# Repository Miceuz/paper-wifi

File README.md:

# Paper-WiFi

Wifi-enabled e-paper display for I2C sensors. Arduino compatible software on Platformio. 3D printable case.

## Specifications

 * MCU: ESP32C3
 * Power supply: 2xAA, 3V
 * Sleep current: 38uA
 * Screen size: 2.13"
 * Display resolution: 212(H) × 104(V) pixels
 * Connectivity: I2C, UART over USB, UART
 * GPIO: 2 
 * Sensors: Temperature, Relative humidity
 * Temperature accuracy: 0.2°C typical
 * Relative humidity accuracy: 1.8% typical

## Programming instructions

Firmware build and upload process is managed by [Platformio](https://platformio.org). Most probably you will encounter the board in deep sleep in which it is not visible via USB. Jump GPIO9 to GND and reset the board to put it into bootloader mode. Run `pio run -t upload` to compile and upload firmware. Remove jumper and reset the board to run. If deep sleep is not used, board can be programmed without GPIO9 jumper.

## MQTT backend infrastructure

 * To quickly see your data piping in follow this guide: [Getting started with MQTT](https://github.com/Miceuz/paper-wifi/tree/main/tutorials/Getting%20started%20with%20MQTT)
 * To setup your own backend for data storage and display follow this guide: [docker-compose-mosquitto-influxdb-telegraf-grafana](https://github.com/Miceuz/docker-compose-mosquitto-influxdb-telegraf-grafana)

## Licence

[CERN Open Hardware Licence Version 2 - Strongly Reciprocal](https://ohwr.org/cern_ohl_s_v2.txt)

![Build with PlatformIO](https://img.shields.io/badge/build%20with-PlatformIO-orange?logo=data%3Aimage%2Fsvg%2Bxml%3Bbase64%2CPHN2ZyB3aWR0aD0iMjUwMCIgaGVpZ2h0PSIyNTAwIiB2aWV3Qm94PSIwIDAgMjU2IDI1NiIgeG1sbnM9Imh0dHA6Ly93d3cudzMub3JnLzIwMDAvc3ZnIiBwcmVzZXJ2ZUFzcGVjdFJhdGlvPSJ4TWlkWU1pZCI+PHBhdGggZD0iTTEyOCAwQzkzLjgxIDAgNjEuNjY2IDEzLjMxNCAzNy40OSAzNy40OSAxMy4zMTQgNjEuNjY2IDAgOTMuODEgMCAxMjhjMCAzNC4xOSAxMy4zMTQgNjYuMzM0IDM3LjQ5IDkwLjUxQzYxLjY2NiAyNDIuNjg2IDkzLjgxIDI1NiAxMjggMjU2YzM0LjE5IDAgNjYuMzM0LTEzLjMxNCA5MC41MS0zNy40OUMyNDIuNjg2IDE5NC4zMzQgMjU2IDE2Mi4xOSAyNTYgMTI4YzAtMzQuMTktMTMuMzE0LTY2LjMzNC0zNy40OS05MC41MUMxOTQuMzM0IDEzLjMxNCAxNjIuMTkgMCAxMjggMCIgZmlsbD0iI0ZGN0YwMCIvPjxwYXRoIGQ9Ik0yNDkuMzg2IDEyOGMwIDY3LjA0LTU0LjM0NyAxMjEuMzg2LTEyMS4zODYgMTIxLjM4NkM2MC45NiAyNDkuMzg2IDYuNjEzIDE5NS4wNCA2LjYxMyAxMjggNi42MTMgNjAuOTYgNjAuOTYgNi42MTQgMTI4IDYuNjE0YzY3LjA0IDAgMTIxLjM4NiA1NC4zNDYgMTIxLjM4NiAxMjEuMzg2IiBmaWxsPSIjRkZGIi8+PHBhdGggZD0iTTE2MC44NjkgNzQuMDYybDUuMTQ1LTE4LjUzN2M1LjI2NC0uNDcgOS4zOTItNC44ODYgOS4zOTItMTAuMjczIDAtNS43LTQuNjItMTAuMzItMTAuMzItMTAuMzJzLTEwLjMyIDQuNjItMTAuMzIgMTAuMzJjMCAzLjc1NSAyLjAxMyA3LjAzIDUuMDEgOC44MzdsLTUuMDUgMTguMTk1Yy0xNC40MzctMy42Ny0yNi42MjUtMy4zOS0yNi42MjUtMy4zOWwtMi4yNTggMS4wMXYxNDAuODcybDIuMjU4Ljc1M2MxMy42MTQgMCA3My4xNzctNDEuMTMzIDczLjMyMy04NS4yNyAwLTMxLjYyNC0yMS4wMjMtNDUuODI1LTQwLjU1NS01Mi4xOTd6TTE0Ni41MyAxNjQuOGMtMTEuNjE3LTE4LjU1Ny02LjcwNi02MS43NTEgMjMuNjQzLTY3LjkyNSA4LjMyLTEuMzMzIDE4LjUwOSA0LjEzNCAyMS41MSAxNi4yNzkgNy41ODIgMjUuNzY2LTM3LjAxNSA2MS44NDUtNDUuMTUzIDUxLjY0NnptMTguMjE2LTM5Ljc1MmE5LjM5OSA5LjM5OSAwIDAgMC05LjM5OSA5LjM5OSA5LjM5OSA5LjM5OSAwIDAgMCA5LjQgOS4zOTkgOS4zOTkgOS4zOTkgMCAwIDAgOS4zOTgtOS40IDkuMzk5IDkuMzk5IDAgMCAwLTkuMzk5LTkuMzk4em0yLjgxIDguNjcyYTIuMzc0IDIuMzc0IDAgMSAxIDAtNC43NDkgMi4zNzQgMi4zNzQgMCAwIDEgMCA0Ljc0OXoiIGZpbGw9IiNFNTcyMDAiLz48cGF0aCBkPSJNMTAxLjM3MSA3Mi43MDlsLTUuMDIzLTE4LjkwMWMyLjg3NC0xLjgzMiA0Ljc4Ni01LjA0IDQuNzg2LTguNzAxIDAtNS43LTQuNjItMTAuMzItMTAuMzItMTAuMzItNS42OTkgMC0xMC4zMTkgNC42Mi0xMC4zMTkgMTAuMzIgMCA1LjY4MiA0LjU5MiAxMC4yODkgMTAuMjY3IDEwLjMxN0w5NS44IDc0LjM3OGMtMTkuNjA5IDYuNTEtNDAuODg1IDIwLjc0Mi00MC44ODUgNTEuODguNDM2IDQ1LjAxIDU5LjU3MiA4NS4yNjcgNzMuMTg2IDg1LjI2N1Y2OC44OTJzLTEyLjI1Mi0uMDYyLTI2LjcyOSAzLjgxN3ptMTAuMzk1IDkyLjA5Yy04LjEzOCAxMC4yLTUyLjczNS0yNS44OC00NS4xNTQtNTEuNjQ1IDMuMDAyLTEyLjE0NSAxMy4xOS0xNy42MTIgMjEuNTExLTE2LjI4IDMwLjM1IDYuMTc1IDM1LjI2IDQ5LjM2OSAyMy42NDMgNjcuOTI2em0tMTguODItMzkuNDZhOS4zOTkgOS4zOTkgMCAwIDAtOS4zOTkgOS4zOTggOS4zOTkgOS4zOTkgMCAwIDAgOS40IDkuNCA5LjM5OSA5LjM5OSAwIDAgMCA5LjM5OC05LjQgOS4zOTkgOS4zOTkgMCAwIDAtOS4zOTktOS4zOTl6bS0yLjgxIDguNjcxYTIuMzc0IDIuMzc0IDAgMSAxIDAtNC43NDggMi4zNzQgMi4zNzQgMCAwIDEgMCA0Ljc0OHoiIGZpbGw9IiNGRjdGMDAiLz48L3N2Zz4=)

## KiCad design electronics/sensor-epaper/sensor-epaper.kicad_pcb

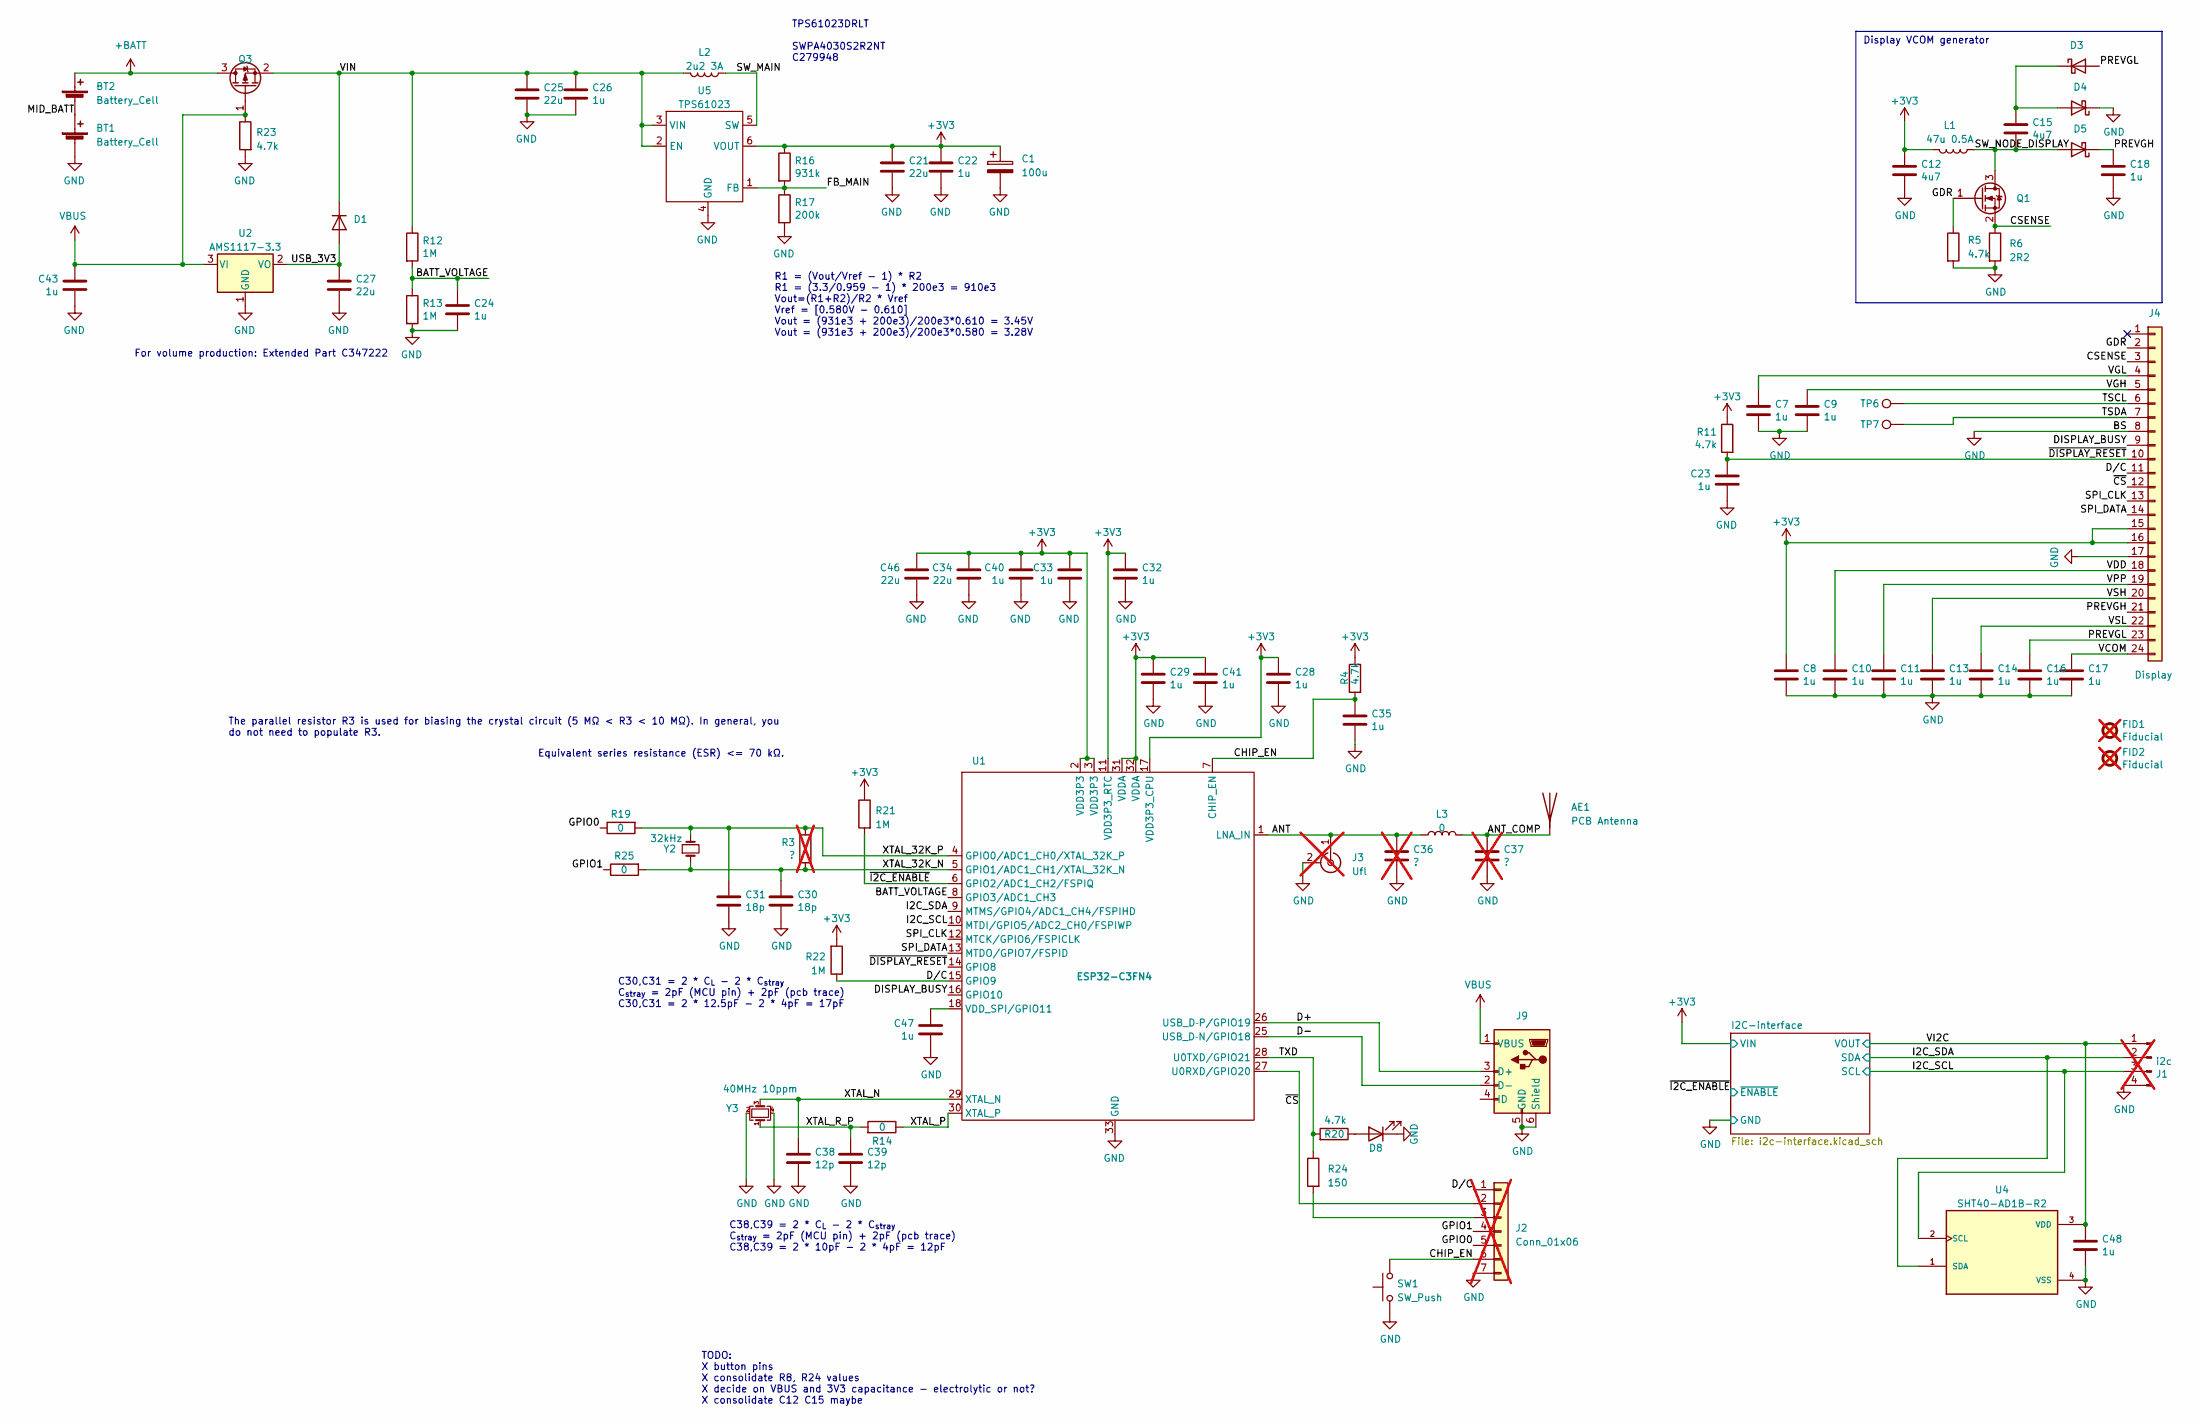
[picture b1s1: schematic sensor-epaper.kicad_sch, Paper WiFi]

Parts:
AE1: PCB Antenna; Texas_SWRA117D_2.4GHz_Left
BT1, BT2: Battery_Cell; AA_KEYCO_53_SMD; PartNo 53
C1: 100u; CP_EIA-3528-15_AVX-H; LCSC C16133
C7, C8, C9, C10, C11, C13, C14, C16, C17, C18, C22, C23, C24, C26, C28, C29, C32, C33, C35, C40, C41, C43, C47, C48: 1u; C_0402_1005Metric; LCSC C52923
C12, C15: 4u7; C_0603_1608Metric; LCSC C19666
C21, C25, C27: 22u; C_0603_1608Metric; PartNo CL10A226MP8NUNE; LCSC C60077
C30, C31: 18p; C_0402_1005Metric; LCSC C33149
C34, C46: 22u; C_0603_1608Metric; LCSC C60077
C36, C37: ?; C_0402_1005Metric; not fitted
C38, C39: 12p; C_0402_1005Metric; LCSC C106201
D1: 2CZ4007; D_SOD-123; LCSC C85712
D3, D4, D5: MBR0530; D_SOD-123; LCSC C8598
D8: LED; LED_0603_1608Metric
FID1, FID2: Fiducial; Fiducial_1mm_Mask2mm; not fitted
J1: i2c; PinHeader_1x04_P1.27mm_Vertical_SMD_Pin1Right; not fitted
J2: Conn_01x06; PinHeader_1x07_P2.54mm_Vertical; not fitted
J3: Ufl; U.FL_Hirose_U.FL-R-SMT-1_Vertical; not fitted
J4: Display; SFV24R-4STE1HLF; PartNo SFV24R-4STE1HLF; LCSC C262643
J9: USB micro; XKB_U254-051T-4BH83-F1S; PartNo U254-051T-4BH83-S1S; LCSC C319160
L1: 47u 0.5A; L_Taiyo-Yuden_NR-40xx; PartNo CKCS4030-47uH/M; LCSC C354593
L2: 2u2 3A; L_Taiyo-Yuden_NR-40xx; PartNo SWPA4030S2R2NT; LCSC C279948
L3: 0; L_0402_1005Metric; LCSC C17168
Q1: Q_NMOS_GSD; SOT-23; LCSC C699302
Q3: NX2301P; SOT-23; PartNo NX2301P,215; LCSC C15127
R3: ?; R_0402_1005Metric; not fitted
R4, R5, R11, R20, R23: 4.7k; R_0603_1608Metric; LCSC C23162
R6: 2R2; R_0603_1608Metric; LCSC C22939
R12, R13, R21, R22: 1M; R_0603_1608Metric; LCSC C22935
R14, R19, R25: 0; R_0402_1005Metric; LCSC C17168
R16: 931k; R_0603_1608Metric; LCSC C322030
R17: 200k; R_0603_1608Metric; LCSC C25811
R24: 150; R_0603_1608Metric; LCSC C22808
SW1: SW_Push; SHOUHAN_TS24CA; PartNo TS24CA; LCSC C393942
TP6, TP7: TestPoint; TestPoint_Pad_D1.5mm
U1: ESP32-C3FN4; QFN-32-1EP_5x5mm_P0.5mm_EP3.7x3.7mm_ThermalVias; LCSC C2858491
U2: AMS1117-3.3; SOT-223-3_TabPin2; LCSC C6186
U4: SHT40-AD1B-R2; Sensirion_SHT40-AD1B-R2
U5: TPS61023; SOT-363_SC-70-6; PartNo TPS61023; LCSC C919459
Y2: 32kHz; Crystal_SMD_2012-2Pin_2.0x1.2mm; PartNo ECS-.327-12.5-12R-TR
Y3: 40MHz 10ppm; Crystal_SMD_2016-4Pin_2.0x1.6mm; PartNo ECS-400-10-37B-CKY-TR

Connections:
+3V3: C1.1, C8.1, C12.1, C21.1, C22.1, C28.1, C29.1, C32.1, C33.1, C34.1, C40.1, C41.1, C46.1, J4.15, J4.16, L1.1, R4.1, R11.1, R16.1, R21.1, R22.2, U1.2 (VDD3P3), U1.3 (VDD3P3), U1.11 (VDD3P3_RTC), U1.17 (VDD3P3_CPU), U1.31 (VDDA), U1.32 (VDDA), U5.6 (VOUT); also elsewhere on the board
+BATT: BT2.1 (+), Q3.3 (D)
/ANT: C36.1, J3.1 (In), L3.1, U1.1 (LNA_IN)
/ANT_COMP: AE1.1 (A), C37.1, L3.2
/BATT_VOLTAGE: C24.1, R12.2, R13.1, U1.8 (GPIO3/ADC1_CH3)
/CHIP_EN: C35.1, J2.6, R4.2, SW1.2, U1.7 (CHIP_EN)
/CSENSE: J4.3, Q1.2 (S), R6.1
/D+: J9.3 (D+), U1.26 (USB_D­P/GPIO19)
/D-: J9.2 (D-), U1.25 (USB_D­N/GPIO18)
/DISPLAY_BUSY: J4.9, U1.16 (GPIO10)
/D/C: J2.1, J4.11, R22.1, U1.15 (GPIO9)
/FB_MAIN: R16.2, R17.1, U5.1 (FB)
/GDR: J4.2, Q1.1 (G), R5.1
/GPIO0: J2.5, R19.1
/GPIO1: J2.4, R25.1
/I2C_SCL: J1.3, U1.10 (MTDI/GPIO5/ADC2_CH0/FSPIWP), U4.2 (SCL); also elsewhere on the board
/I2C_SDA: J1.2, U1.9 (MTMS/GPIO4/ADC1_CH4/FSPIHD), U4.1 (SDA); also elsewhere on the board
/MID_BATT: BT1.1 (+), BT2.2 (-)
/PREVGH: C18.1, D5.1 (K), J4.21
/PREVGL: C16.1, D3.2 (A), J4.23
/SPI_CLK: J4.13, U1.12 (MTCK/GPIO6/FSPICLK)
/SPI_DATA: J4.14, U1.13 (MTDO/GPIO7/FSPID)
/SW_MAIN: L2.2, U5.5 (SW)
/SW_NODE_DISPLAY: C15.2, D5.2 (A), L1.2, Q1.3 (D)
/TSCL: J4.6, TP6.1
/TSDA: J4.7, TP7.1
/TXD: R20.2, R24.1, U1.28 (U0TXD/GPIO21)
/USB_3V3: C27.1, D1.2 (A), U2.2 (VO)
/VCOM: C17.1, J4.24
/VDD: C10.1, J4.18
/VGH: C9.1, J4.5
/VGL: C7.1, J4.4
/VI2C: C48.1, J1.1, U4.3 (VDD); also elsewhere on the board
/VIN: C25.1, C26.1, D1.1 (K), L2.1, Q3.2 (S), R12.1, U5.2 (EN), U5.3 (VIN)
/VPP: C11.1, J4.19
/VSH: C13.1, J4.20
/VSL: C14.1, J4.22
/XTAL_32K_N: C30.1, R3.2, R25.2, U1.5 (GPIO1/ADC1_CH1/XTAL_32K_N), Y2.1
/XTAL_32K_P: C31.1, R3.1, R19.2, U1.4 (GPIO0/ADC1_CH0/XTAL_32K_P), Y2.2
/XTAL_N: C38.1, U1.29 (XTAL_N), Y3.3
/XTAL_P: R14.1, U1.30 (XTAL_P)
/XTAL_R_P: C39.1, R14.2, Y3.1
/~CS: J2.2, J4.12, U1.27 (U0RXD/GPIO20)
/~DISPLAY_RESET: C23.1, J4.10, R11.2, U1.14 (GPIO8)
/~I2C_ENABLE: R21.2, U1.6 (GPIO2/ADC1_CH2/FSPIQ); also elsewhere on the board
GND: BT1.2 (-), C1.2, C7.2, C8.2, C9.2, C10.2, C11.2, C12.2, C13.2, C14.2, C16.2, C17.2, C18.2, C21.2, C22.2, C23.2, C24.2, C25.2, C26.2, C27.2, C28.2, C29.2, C30.2, C31.2, C32.2, C33.2, C34.2, C35.2, C36.2, C37.2, C38.2, C39.2, C40.2, C41.2, C43.2, C46.2, C47.2, C48.2, D4.1 (K), D8.1 (K), J1.4, J2.7, J3.2 (Ext), J4.8, J4.17, J9.5 (GND), J9.6 (Shield), R5.2, R6.2, R13.2, R17.2, R23.2, SW1.1, U1.33 (GND), U2.1 (GND), U4.4 (VSS), U5.4 (GND), Y3.2, Y3.4
unnamed: C15.1, D3.1 (K), D4.2 (A)
unnamed: D8.2 (A), R20.1
unnamed: J2.3, R24.2
unnamed: C47.1, U1.18 (VDD_SPI/GPIO11)
VBUS: C43.1, J9.1 (VBUS), Q3.1 (G), R23.1, U2.3 (VI)

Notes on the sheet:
R1 = (Vout/Vref - 1) * R2 R1 = (3.3/0.959 - 1) * 200e3 = 910e3 Vout=(R1+R2)/R2 * Vref Vref = [0.580V - 0.610] Vout = (931e3 + 200e3)/200e3*0.610 = 3.45V Vout = (931e3 + 200e3)/200e3*0.580 = 3.28V
Equivalent series resistance (ESR) <= 70 kΩ.
TODO: X button pins X consolidate R8, R24 values X decide on VBUS and 3V3 capacitance - electrolytic or not? X consolidate C12 C15 maybe
For volume production: Extended Part C347222
The parallel resistor R3 is used for biasing the crystal circuit (5 MΩ < R3 < 10 MΩ). In general, you do not need to populate R3.
Display VCOM generator
TPS61023DRLT SWPA4030S2R2NT C279948
C30,C31 = 2 * C_{L} - 2 * C_{stray} C_{stray} = 2pF (MCU pin) + 2pF (pcb trace) C30,C31 = 2 * 12.5pF - 2 * 4pF = 17pF
C38,C39 = 2 * C_{L} - 2 * C_{stray} C_{stray} = 2pF (MCU pin) + 2pF (pcb trace) C38,C39 = 2 * 10pF - 2 * 4pF = 12pF

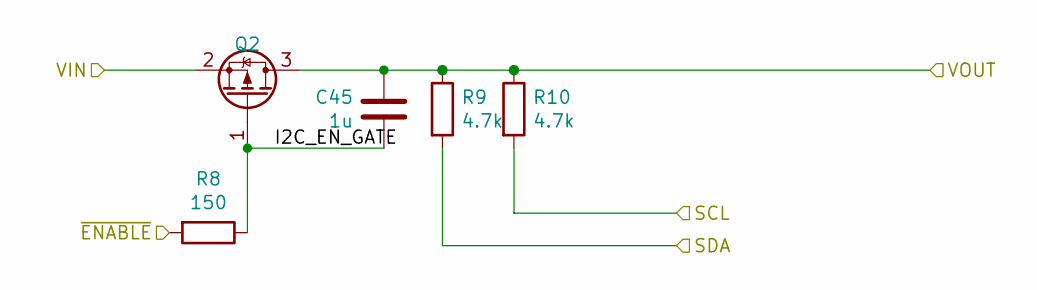
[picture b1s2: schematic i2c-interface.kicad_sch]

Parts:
C45: 1u; C_0402_1005Metric; LCSC C52923
Q2: NX2301P; SOT-23; PartNo NX2301P,215; LCSC C15127
R8: 150; R_0603_1608Metric; LCSC C22808
R9, R10: 4.7k; R_0603_1608Metric; LCSC C23162

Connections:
+3V3: Q2.2 (S); also elsewhere on the board
/I2C-interface/I2C_EN_GATE: C45.2, Q2.1 (G), R8.1
/I2C_SCL: R10.2; also elsewhere on the board
/I2C_SDA: R9.2; also elsewhere on the board
/VI2C: C45.1, Q2.3 (D), R9.1, R10.1; also elsewhere on the board
/~I2C_ENABLE: R8.2; also elsewhere on the board

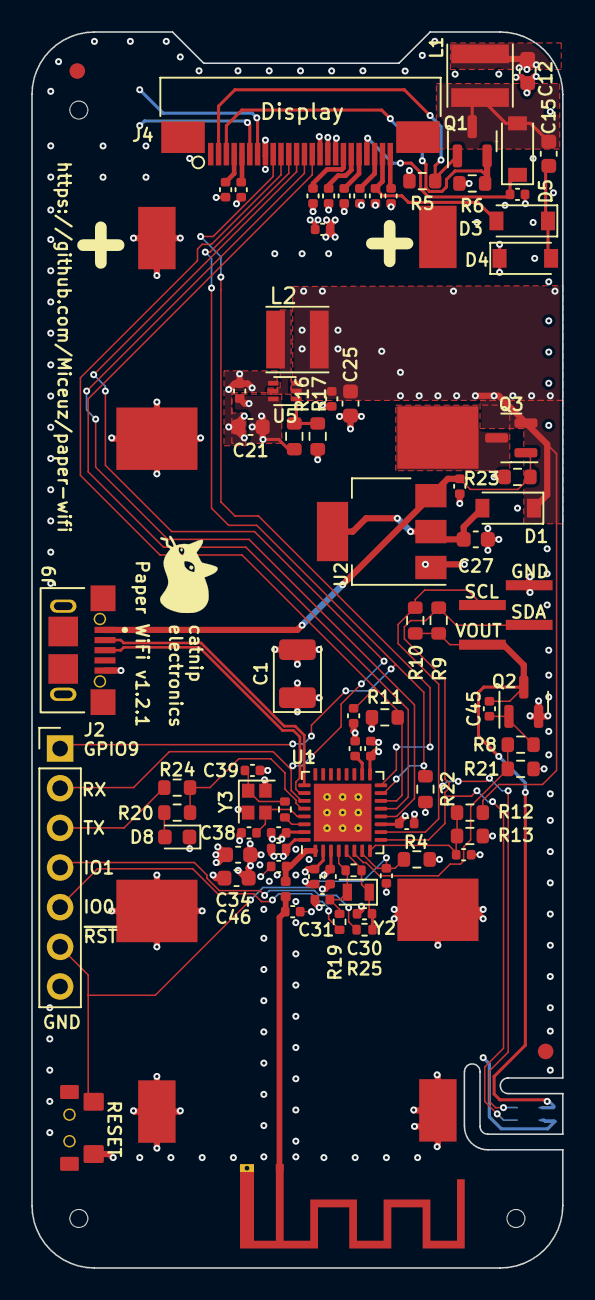
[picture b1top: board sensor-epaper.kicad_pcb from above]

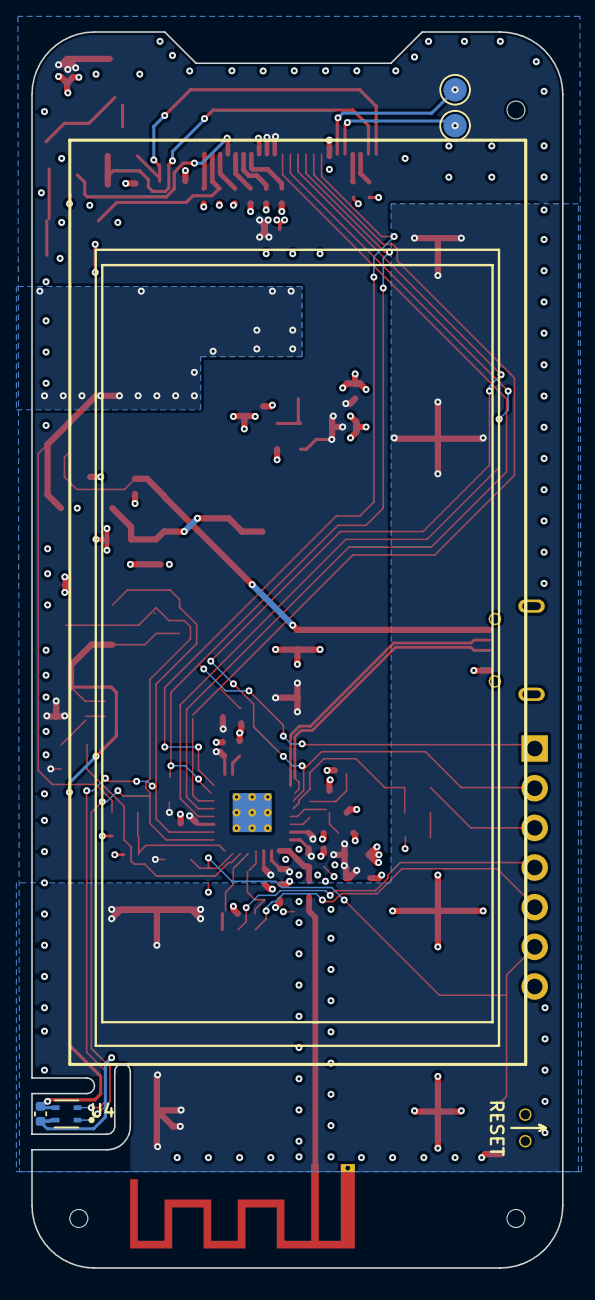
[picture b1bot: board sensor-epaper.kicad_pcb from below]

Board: 4 copper layers, 34.0 x 79.2 mm, 91 parts (4 on the bottom side), 52 nets.

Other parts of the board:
H6, H6#2, H6#3: ToolingHole; JLC_ToolingHole

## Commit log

2022-01-22 initial
2022-01-22 Add relevant documentation
2022-01-22 Add mechanical stuff - drawings of case and test assemblies
2022-01-22 add a pic for documentation
2022-10-27 Add various firmware experiments
2022-10-27 Implement fixes for v1.0.0 board: * Fixed mirrored display connector * Fixed wrong button pinout * Remove CS from GPIO11 which is VDD_SPI after all, add a requisite cap * Add tantallum bulk cap, add 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
2022-10-27 Add more documentation
2022-11-09 Add custom size bigger fonts
2022-11-09 Average readings, use bigger font
2022-11-09 Add explicit partitioning settings.
2022-11-09 Shuffle stuff on User Comments layer, hunt kicad format changes
2022-11-09 Add case
2022-11-09 add some badges
2022-11-09 Remove autogenerated file
2022-11-19 Update readme with pic
2022-11-19 More readme
2022-12-05 Add deep sleep current
2022-12-05 Tidy up mechanical folder
2022-12-05 Add SHT40 demo firmware
2022-12-05 Add cutout in the PCB to decouple SHT40, fix GND connection
2022-12-06 More tidying up of the code with regards to parammeter passing and additional config items like mqtt password and port
2022-12-06 Refactor soil moisture sensor example firmware a bit
2022-12-06 Add missed electronics files for PCB 1.2.0
2022-12-06 Add enclosure files for pcb 1.2.0
2022-12-14 Refactor code more, fix some corner cases
2022-12-14 Rename the official examples
2022-12-15 Work around AP creation issues that still manifest in some cases
2022-12-15 Send moisture as int via mqtt
2022-12-15 Change settings fields to plain types so that they are saved to RTC memory during deep sleep.
2022-12-15 Only single decimal digit makes sense in soil moisture
2022-12-15 Perform measurement once in 5 min
2022-12-15 Migrate previous changes to humidity sensor example
2022-12-15 Add SHT40 isolated test
2022-12-15 Update pictures, add licence
2022-12-16 Fix WifiManager version
2022-12-16 Refactor even more: move format conversion to SensoeReadings, use global settings in display
2022-12-19 Work around a situation where previously configured WiFi network is not accessible anymore and WiFi manager config portal is started silently. Now don't star config portal and give up after 3 tries. 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
2022-12-19 Fix a bug where temperature units were printed as string while they are char
2022-12-19 Add an option for primary/secondary reading display
2022-12-19 Ignore vscode stuff
2022-12-19 Set default settings if they were not set via config portal
2022-12-20 Add latest fixes and features to humidity display firmware
2022-12-20 Remove vscode stuff
2022-12-24 Add a silkscreen for git repo
2023-01-04 Add basic MQTT tutorial
2023-01-04 Update README.md
    Make images work
2023-01-04 Change DC/DC regulator to TPS61023 as previous one is out of stock. Change L1 and R6 to accomodate another display as previous one will be end of life soon
2023-01-11 Update README.md
    Add links to mqtt tutorials
2023-02-18 Put correct resistor into Dc/Dc converters divider. Fix SC70 footprint
2023-02-18 Add a link to useful utility
2023-02-18 Use c++ average library instead of verbatim averaging
2023-02-25 Update README.md
    fix spelling
2023-03-07 Fix 3d model rotation
2023-03-07 Fix antenna trace so it's 50 Ohm
2023-03-08 Move to GDEY0213B74 display
2023-03-08 Get rid of .ino file so vscode does not complain
2023-03-08 Add BLE peripheral example
2023-09-20 Impove soil moisture sensor example - new display, no debug delay, better batterylife
2023-10-21 Add pullup and interrupt listener on IO0
2023-10-21 Configure wake up pin for deep sleep
2023-10-21 Add wakeup pin to soil moisture example
2023-10-21 Slow down I2C clock so we are more robust against long cables
